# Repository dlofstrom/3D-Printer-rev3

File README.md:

# 3D Printer rev3

This repository contains all the source files for my 3D printer

More details about the build can be found at dlofstrom.wordpress.com

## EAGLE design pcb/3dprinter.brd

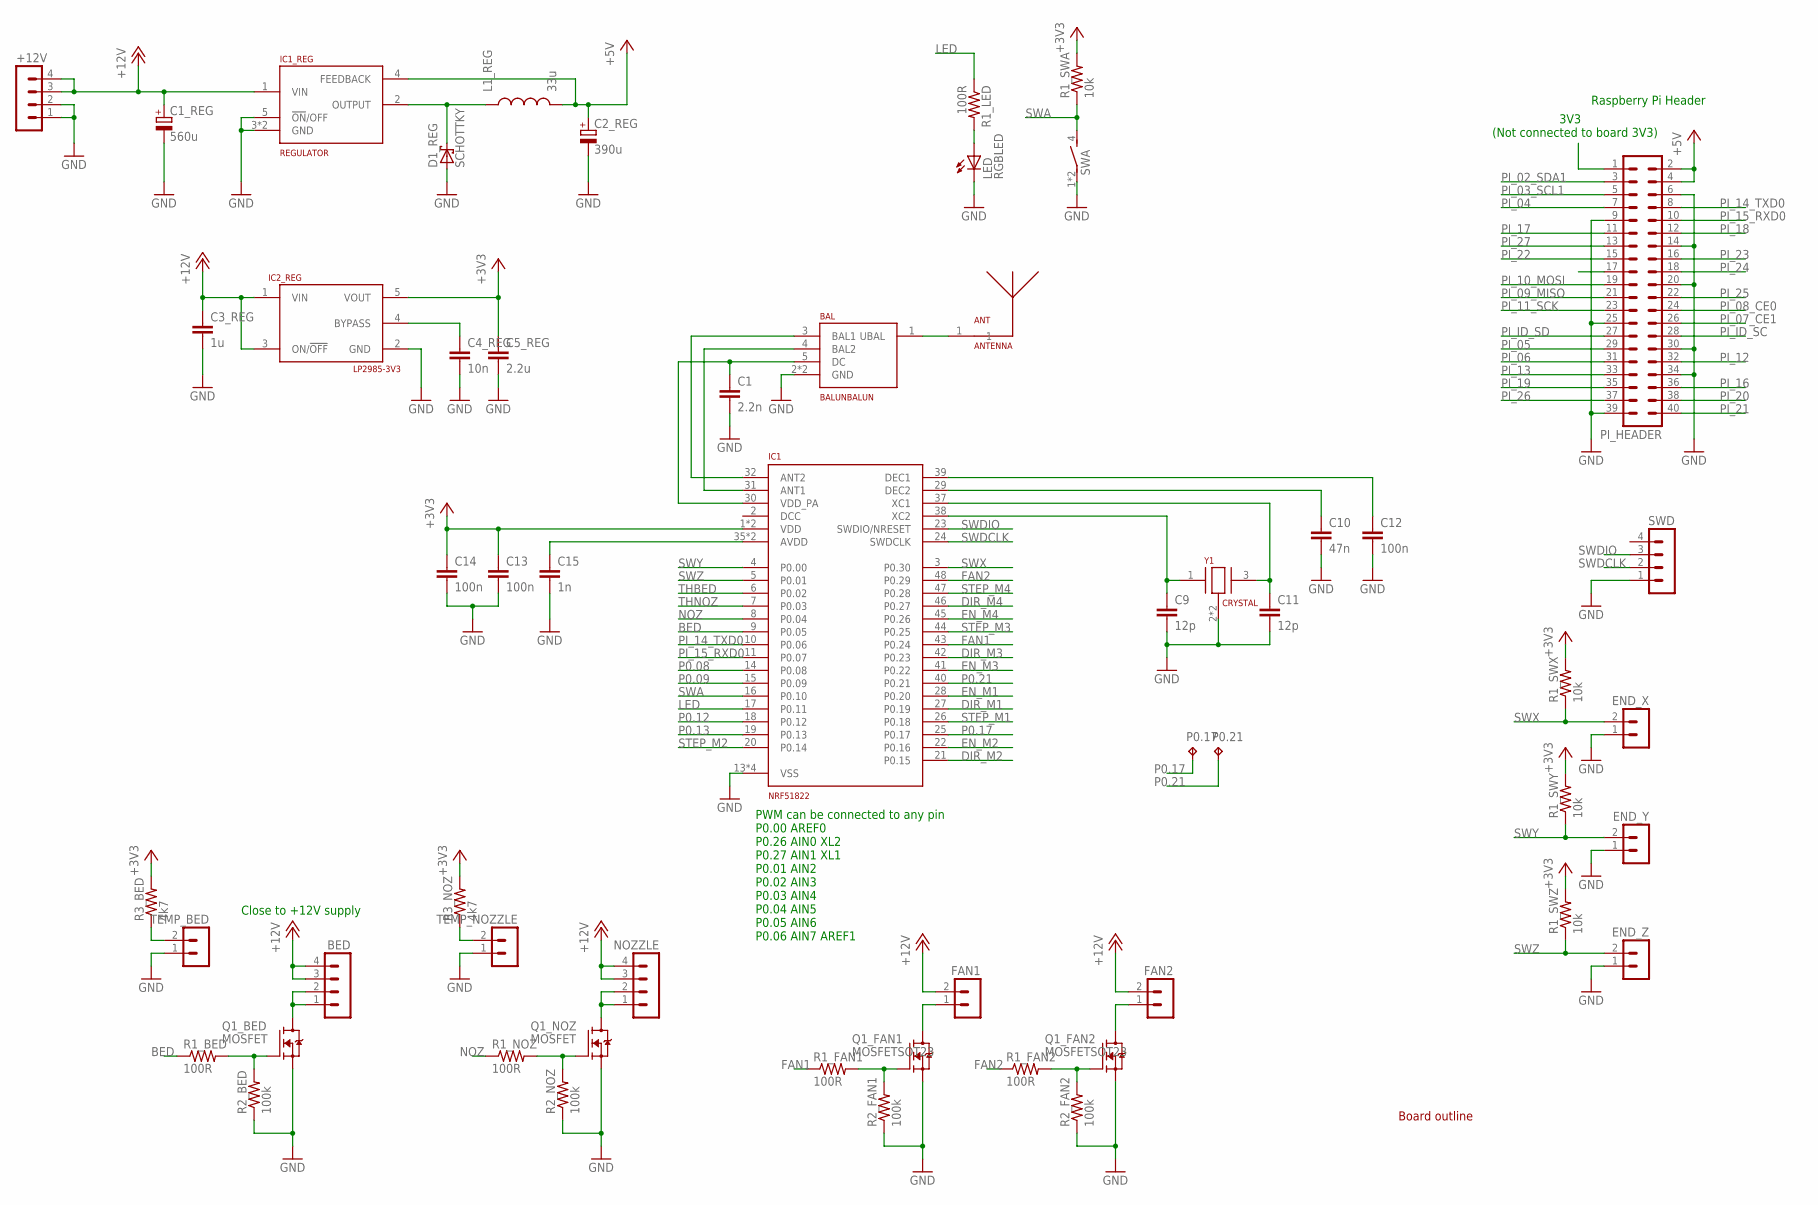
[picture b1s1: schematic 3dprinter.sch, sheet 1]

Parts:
+12V: MA04-15.08; MA04-1_5MM
ANT: ANTENNA
BAL: BALUNBALUN; BALUN
BED: MA04-12.54; MA04-1
C1: 2.2n; C0603
C1_REG: 560u; TANTULUM
C2_REG: 390u; TANTULUM
C3_REG: 1u; C0805
C4_REG: 10n; C0603
C5_REG: 2.2u; C0805
C9, C11: 12p; C0603
C10: 47n; C0603
C12, C13, C14: 100n; C0603
C15: 1n; C0603
D1_REG: SCHOTTKY
END_X: MA02-12.54; MA02-1
END_Y: MA02-12.54; MA02-1
END_Z: MA02-12.54; MA02-1
FAN1, FAN2: MA02-12.54; MA02-1
IC1: NRF51822; QFN48
IC1_REG: REGULATOR
IC2_REG: LP2985-3V3; SOT23
L1_REG: 33u; INDUCTOR
LED: RGBLED
NOZZLE: MA04-12.54; MA04-1
OUTLINE: OUTLINE
P0.17, P0.21: TPB1,27; B1,27
PI_HEADER: MA20-2
Q1_BED, Q1_NOZ: MOSFET
Q1_FAN1, Q1_FAN2: MOSFETSOT23; SOT23_FAN
R1_BED, R1_FAN1, R1_FAN2, R1_LED, R1_NOZ: 100R; R0603
R1_SWA, R1_SWX, R1_SWY, R1_SWZ: 10k; R0603
R2_BED, R2_FAN1, R2_FAN2, R2_NOZ: 100k; R0603
R3_BED, R3_NOZ: 4k7; R0603
SWA: BUTTON
SWD: MA04-12.54; MA04-1
TEMP_BED: MA02-12.54; MA02-1
TEMP_NOZZLE: MA02-12.54; MA02-1
Y1: CRYSTAL

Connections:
+3V3: C5_REG.1, C13.1, C14.1, IC1.1 (VDD), IC1.12 (VDD), IC2_REG.5 (VOUT), R1_SWA.2, R1_SWX.2, R1_SWY.2, R1_SWZ.2, R3_BED.2, R3_NOZ.2; also elsewhere on the board
+5V: C2_REG.+, IC1_REG.4 (FEEDBACK), L1_REG.2, PI_HEADER.2, PI_HEADER.4
+12V: +12V.3, +12V.4, BED.3, BED.4, C1_REG.+, C3_REG.1, FAN1.2, FAN2.2, IC1_REG.1 (VIN), IC2_REG.1 (VIN), IC2_REG.3 (ON/!OFF), NOZZLE.3, NOZZLE.4; also elsewhere on the board
ANT: ANT.1, BAL.1 (UBAL)
BED: IC1.9 (P0.05), R1_BED.1
BED-: BED.1, BED.2, Q1_BED.TAB (D)
BEDG: Q1_BED.4 (G), R1_BED.2, R2_BED.2
DIR_M1: IC1.27 (P0.19); also elsewhere on the board
DIR_M2: IC1.21 (P0.15); also elsewhere on the board
DIR_M3: IC1.42 (P0.23); also elsewhere on the board
DIR_M4: IC1.46 (P0.27); also elsewhere on the board
EN_M1: IC1.28 (P0.20); also elsewhere on the board
EN_M2: IC1.22 (P0.16); also elsewhere on the board
EN_M3: IC1.41 (P0.22); also elsewhere on the board
EN_M4: IC1.45 (P0.26); also elsewhere on the board
FAN1: IC1.43 (P0.24), R1_FAN1.1
FAN1-: FAN1.1, Q1_FAN1.3 (D)
FAN1G: Q1_FAN1.1 (G), R1_FAN1.2, R2_FAN1.2
FAN2: IC1.48 (P0.29), R1_FAN2.1
FAN2-: FAN2.1, Q1_FAN2.3 (D)
FAN2G: Q1_FAN2.1 (G), R1_FAN2.2, R2_FAN2.2
GND: +12V.1, +12V.2, BAL.2 (GND), BAL.6 (GND), C1.2, C1_REG.-, C2_REG.-, C3_REG.2, C4_REG.2, C5_REG.2, C9.2, C10.2, C11.2, C12.2, C13.2, C14.2, C15.2, D1_REG.A, END_X.1, END_Y.1, END_Z.1, IC1.13 (VSS), IC1.33 (VSS), IC1.34 (VSS), IC1.PAD (VSS), IC1_REG.3 (GND), IC1_REG.5 (!ON!/OFF), IC1_REG.TAB (GND), IC2_REG.2 (GND), LED.C, PI_HEADER.6, PI_HEADER.9, PI_HEADER.14, PI_HEADER.20, PI_HEADER.25, PI_HEADER.30, PI_HEADER.34, PI_HEADER.39, Q1_BED.1 (S), Q1_BED.2 (S), Q1_BED.3 (S), Q1_FAN1.2 (S), Q1_FAN2.2 (S), Q1_NOZ.1 (S), Q1_NOZ.2 (S), Q1_NOZ.3 (S), R2_BED.1, R2_FAN1.1, R2_FAN2.1, R2_NOZ.1, SWA.1, SWA.2 (1), SWD.1, TEMP_BED.1, TEMP_NOZZLE.1, Y1.2, Y1.4 (2); also elsewhere on the board
IC1_ANT1: BAL.3 (BAL1), IC1.32 (ANT2)
IC1_ANT2: BAL.4 (BAL2), IC1.31 (ANT1)
IC1_AVDD: C15.1, IC1.35 (AVDD), IC1.36 (AVDD)
IC1_DEC1: C12.1, IC1.39 (DEC1)
IC1_DEC2: C10.1, IC1.29 (DEC2)
IC1_REG_OUT: D1_REG.C, IC1_REG.2 (OUTPUT), L1_REG.1
IC1_VDD_PA: BAL.5 (DC), C1.1, IC1.30 (VDD_PA)
IC1_XC1: C11.1, IC1.37 (XC1), Y1.3
IC1_XC2: C9.1, IC1.38 (XC2), Y1.1
IC2_REG_BYPASS: C4_REG.1, IC2_REG.4 (BYPASS)
LED: IC1.17 (P0.11), R1_LED.1
LEDA: LED.A, R1_LED.2
NOZ: IC1.8 (P0.04), R1_NOZ.1
NOZ-: NOZZLE.1, NOZZLE.2, Q1_NOZ.TAB (D)
NOZG: Q1_NOZ.4 (G), R1_NOZ.2, R2_NOZ.2
P0.08: IC1.14 (P0.08)
P0.09: IC1.15 (P0.09)
P0.12: IC1.18 (P0.12)
P0.13: IC1.19 (P0.13)
P0.17: IC1.25 (P0.17), P0.17.TP
P0.21: IC1.40 (P0.21), P0.21.TP
PI_02_SDA1: PI_HEADER.3
PI_3V3: PI_HEADER.1
PI_3V32: PI_HEADER.17
PI_03_SCL1: PI_HEADER.5
PI_04: PI_HEADER.7
PI_05: PI_HEADER.29
PI_06: PI_HEADER.31
PI_07_CE1: PI_HEADER.26
PI_08_CE0: PI_HEADER.24
PI_09_MISO: PI_HEADER.21
PI_10_MOSI: PI_HEADER.19
PI_11_SCK: PI_HEADER.23
PI_12: PI_HEADER.32
PI_13: PI_HEADER.33
PI_14_TXD0: IC1.10 (P0.06), PI_HEADER.8
PI_15_RXD0: IC1.11 (P0.07), PI_HEADER.10
PI_16: PI_HEADER.36
PI_17: PI_HEADER.11
PI_18: PI_HEADER.12
PI_19: PI_HEADER.35
PI_20: PI_HEADER.38
PI_21: PI_HEADER.40
PI_22: PI_HEADER.15
PI_23: PI_HEADER.16
PI_24: PI_HEADER.18
PI_25: PI_HEADER.22
PI_26: PI_HEADER.37
PI_27: PI_HEADER.13
PI_ID_SC: PI_HEADER.28
PI_ID_SD: PI_HEADER.27
STEP_M1: IC1.26 (P0.18); also elsewhere on the board
STEP_M2: IC1.20 (P0.14); also elsewhere on the board
STEP_M3: IC1.44 (P0.25); also elsewhere on the board
STEP_M4: IC1.47 (P0.28); also elsewhere on the board
SWA: IC1.16 (P0.10), R1_SWA.1, SWA.4 (2)
SWDCLK: IC1.24 (SWDCLK), SWD.2
SWDIO: IC1.23 (SWDIO/NRESET), SWD.3
SWX: END_X.2, IC1.3 (P0.30), R1_SWX.1
SWY: END_Y.2, IC1.4 (P0.00), R1_SWY.1
SWZ: END_Z.2, IC1.5 (P0.01), R1_SWZ.1
THBED: IC1.6 (P0.02), R3_BED.1, TEMP_BED.2
THNOZ: IC1.7 (P0.03), R3_NOZ.1, TEMP_NOZZLE.2

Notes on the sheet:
Raspberry Pi Header
3V3 (Not connected to board 3V3)
Close to +12V supply
PWM can be connected to any pin P0.00 AREF0 P0.26 AIN0 XL2 P0.27 AIN1 XL1 P0.01 AIN2 P0.02 AIN3 P0.03 AIN4 P0.04 AIN5 P0.05 AIN6 P0.06 AIN7 AREF1

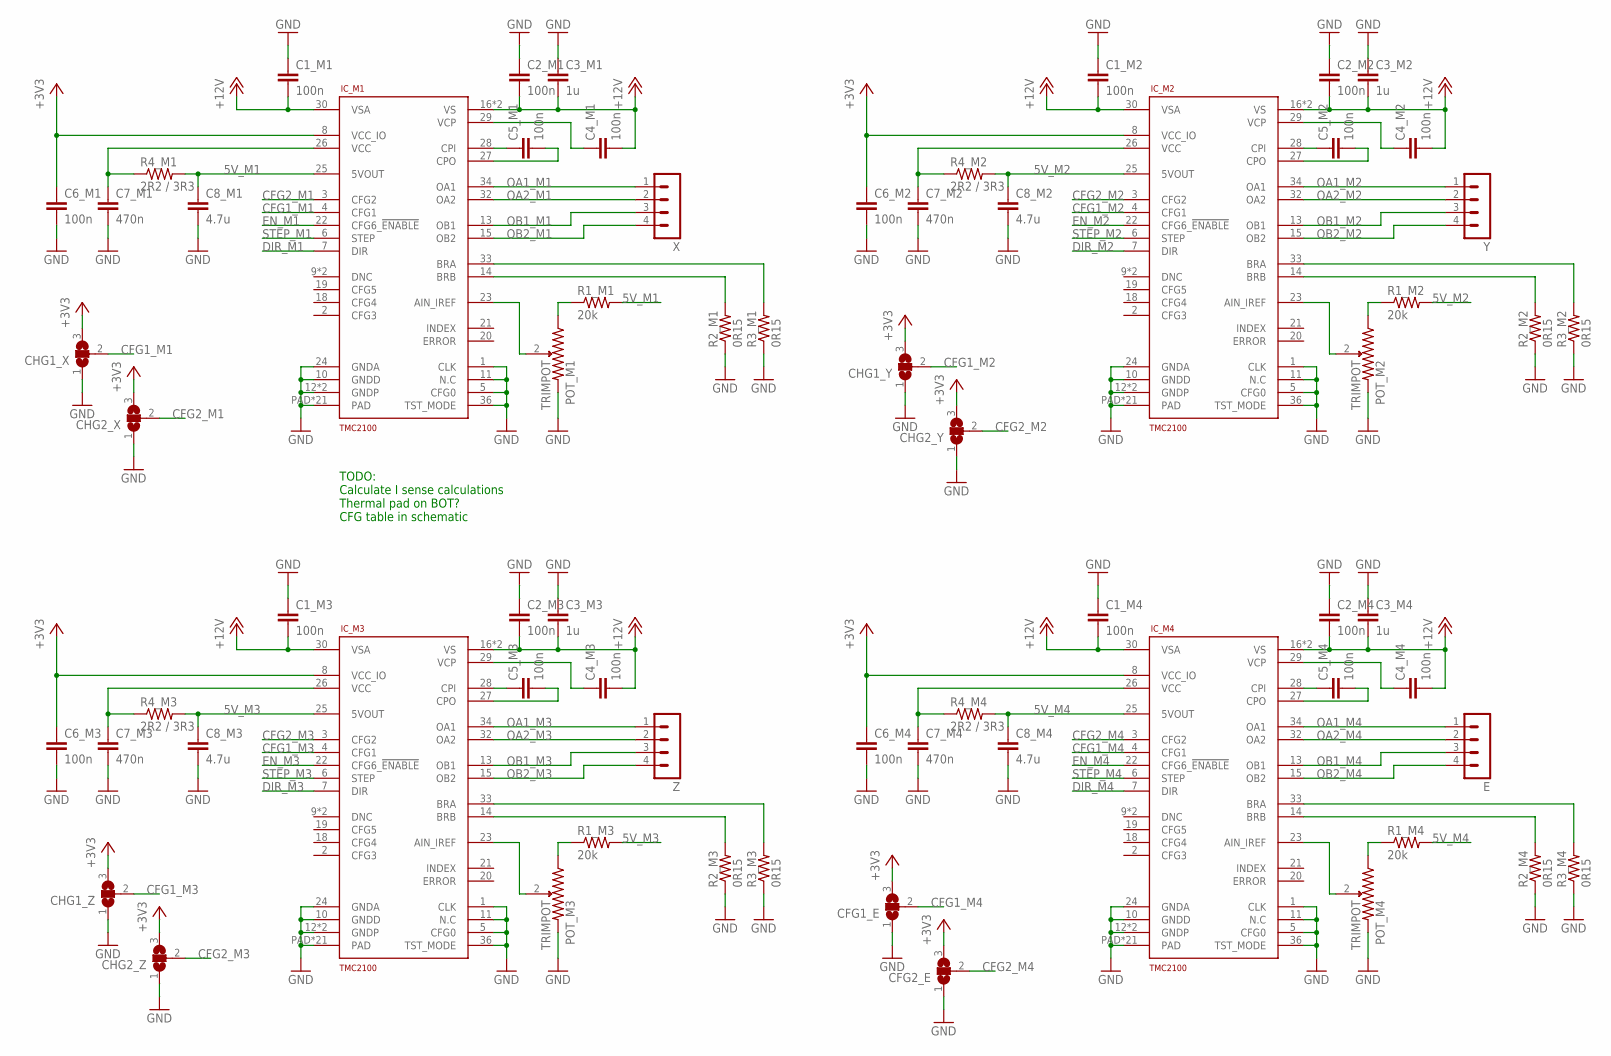
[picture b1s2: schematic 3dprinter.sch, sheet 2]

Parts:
C1_M1, C1_M2, C1_M3, C1_M4, C2_M1, C2_M2, C2_M3, C2_M4, C4_M1, C4_M2, C4_M3, C4_M4, C5_M1, C5_M2, C5_M3, C5_M4, C6_M1, C6_M2, C6_M3, C6_M4: 100n; C0603
C3_M1, C3_M2, C3_M3, C3_M4: 1u; C0603
C7_M1, C7_M2, C7_M3, C7_M4: 470n; C0603
C8_M1, C8_M2, C8_M3, C8_M4: 4.7u; C0603
CFG1_E, CFG2_E: SJ2W; SJ_2
CHG1_X, CHG1_Y, CHG1_Z, CHG2_X, CHG2_Y, CHG2_Z: SJ2W; SJ_2
E: MA04-12.54; MA04-1
IC_M1, IC_M2, IC_M3, IC_M4: TMC2100; QFN36
POT_M1, POT_M2, POT_M3, POT_M4: TRIMPOT
R1_M1, R1_M2, R1_M3, R1_M4: 20k; R0603
R2_M1, R2_M2, R2_M3, R2_M4, R3_M1, R3_M2, R3_M3, R3_M4: 0R15; R0805
R4_M1, R4_M2, R4_M3, R4_M4: 2R2 / 3R3; R0603
X: MA04-12.54; MA04-1
Y: MA04-12.54; MA04-1
Z: MA04-12.54; MA04-1

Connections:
5V_M1: C8_M1.1, IC_M1.25 (5VOUT), R1_M1.2, R4_M1.2
5V_M2: C8_M2.1, IC_M2.25 (5VOUT), R1_M2.2, R4_M2.2
5V_M3: C8_M3.1, IC_M3.25 (5VOUT), R1_M3.2, R4_M3.2
5V_M4: C8_M4.1, IC_M4.25 (5VOUT), R1_M4.2, R4_M4.2
+3V3: C6_M1.1, C6_M2.1, C6_M3.1, C6_M4.1, CFG1_E.3, CFG2_E.3, CHG1_X.3, CHG1_Y.3, CHG1_Z.3, CHG2_X.3, CHG2_Y.3, CHG2_Z.3, IC_M1.8 (VCC_IO), IC_M2.8 (VCC_IO), IC_M3.8 (VCC_IO), IC_M4.8 (VCC_IO); also elsewhere on the board
+12V: C1_M1.2, C1_M2.2, C1_M3.2, C1_M4.2, C2_M1.2, C2_M2.2, C2_M3.2, C2_M4.2, C3_M1.2, C3_M2.2, C3_M3.2, C3_M4.2, C4_M1.2, C4_M2.2, C4_M3.2, C4_M4.2, IC_M1.16 (VS), IC_M1.30 (VSA), IC_M1.31 (VS), IC_M2.16 (VS), IC_M2.30 (VSA), IC_M2.31 (VS), IC_M3.16 (VS), IC_M3.30 (VSA), IC_M3.31 (VS), IC_M4.16 (VS), IC_M4.30 (VSA), IC_M4.31 (VS); also elsewhere on the board
AIN_M1: IC_M1.23 (AIN_IREF), POT_M1.2
AIN_M2: IC_M2.23 (AIN_IREF), POT_M2.2
AIN_M3: IC_M3.23 (AIN_IREF), POT_M3.2
AIN_M4: IC_M4.23 (AIN_IREF), POT_M4.2
BRA_M1: IC_M1.33 (BRA), R3_M1.2
BRA_M2: IC_M2.33 (BRA), R3_M2.2
BRA_M3: IC_M3.33 (BRA), R3_M3.2
BRA_M4: IC_M4.33 (BRA), R3_M4.2
BRB_M1: IC_M1.14 (BRB), R2_M1.2
BRB_M2: IC_M2.14 (BRB), R2_M2.2
BRB_M3: IC_M3.14 (BRB), R2_M3.2
BRB_M4: IC_M4.14 (BRB), R2_M4.2
CFG1_M1: CHG1_X.2, IC_M1.4 (CFG1)
CFG1_M2: CHG1_Y.2, IC_M2.4 (CFG1)
CFG1_M3: CHG1_Z.2, IC_M3.4 (CFG1)
CFG1_M4: CFG1_E.2, IC_M4.4 (CFG1)
CFG2_M1: CHG2_X.2, IC_M1.3 (CFG2)
CFG2_M2: CHG2_Y.2, IC_M2.3 (CFG2)
CFG2_M3: CHG2_Z.2, IC_M3.3 (CFG2)
CFG2_M4: CFG2_E.2, IC_M4.3 (CFG2)
CPI_M1: C5_M1.1, IC_M1.28 (CPI)
CPI_M2: C5_M2.1, IC_M2.28 (CPI)
CPI_M3: C5_M3.1, IC_M3.28 (CPI)
CPI_M4: C5_M4.1, IC_M4.28 (CPI)
CPO_M1: C5_M1.2, IC_M1.27 (CPO)
CPO_M2: C5_M2.2, IC_M2.27 (CPO)
CPO_M3: C5_M3.2, IC_M3.27 (CPO)
CPO_M4: C5_M4.2, IC_M4.27 (CPO)
DIR_M1: IC_M1.7 (DIR); also elsewhere on the board
DIR_M2: IC_M2.7 (DIR); also elsewhere on the board
DIR_M3: IC_M3.7 (DIR); also elsewhere on the board
DIR_M4: IC_M4.7 (DIR); also elsewhere on the board
EN_M1: IC_M1.22 (CFG6_!ENABLE); also elsewhere on the board
EN_M2: IC_M2.22 (CFG6_!ENABLE); also elsewhere on the board
EN_M3: IC_M3.22 (CFG6_!ENABLE); also elsewhere on the board
EN_M4: IC_M4.22 (CFG6_!ENABLE); also elsewhere on the board
GND: C1_M1.1, C1_M2.1, C1_M3.1, C1_M4.1, C2_M1.1, C2_M2.1, C2_M3.1, C2_M4.1, C3_M1.1, C3_M2.1, C3_M3.1, C3_M4.1, C6_M1.2, C6_M2.2, C6_M3.2, C6_M4.2, C7_M1.2, C7_M2.2, C7_M3.2, C7_M4.2, C8_M1.2, C8_M2.2, C8_M3.2, C8_M4.2, CFG1_E.1, CFG2_E.1, CHG1_X.1, CHG1_Y.1, CHG1_Z.1, CHG2_X.1, CHG2_Y.1, CHG2_Z.1, IC_M1.1 (CLK), IC_M1.5 (CFG0), IC_M1.10 (GNDD), IC_M1.11 (N.C), IC_M1.12 (GNDP), IC_M1.24 (GNDA), IC_M1.35 (GNDP), IC_M1.36 (TST_MODE), IC_M1.PAD, IC_M1.TVIA1 (PAD), IC_M1.TVIA2 (PAD), IC_M1.TVIA3 (PAD), IC_M1.TVIA4 (PAD), IC_M1.TVIA5 (PAD), IC_M1.TVIA6 (PAD), IC_M1.TVIA7 (PAD), IC_M1.TVIA8 (PAD), IC_M1.TVIA9 (PAD), IC_M1.TVIA10 (PAD), IC_M1.TVIA11 (PAD), IC_M1.TVIA12 (PAD), IC_M1.TVIA13 (PAD), IC_M1.TVIA14 (PAD), IC_M1.TVIA15 (PAD), IC_M1.TVIA16 (PAD), IC_M1.TVIA17 (PAD), IC_M1.TVIA18 (PAD), IC_M1.TVIA19 (PAD), IC_M1.TVIA20 (PAD), IC_M2.1 (CLK), IC_M2.5 (CFG0), IC_M2.10 (GNDD), IC_M2.11 (N.C), IC_M2.12 (GNDP), IC_M2.24 (GNDA), IC_M2.35 (GNDP), IC_M2.36 (TST_MODE), IC_M2.PAD, IC_M2.TVIA1 (PAD), IC_M2.TVIA2 (PAD), IC_M2.TVIA3 (PAD), IC_M2.TVIA4 (PAD), IC_M2.TVIA5 (PAD), IC_M2.TVIA6 (PAD), IC_M2.TVIA7 (PAD), IC_M2.TVIA8 (PAD), IC_M2.TVIA9 (PAD), IC_M2.TVIA10 (PAD), IC_M2.TVIA11 (PAD), IC_M2.TVIA12 (PAD), IC_M2.TVIA13 (PAD), IC_M2.TVIA14 (PAD), IC_M2.TVIA15 (PAD), IC_M2.TVIA16 (PAD), IC_M2.TVIA17 (PAD), IC_M2.TVIA18 (PAD), IC_M2.TVIA19 (PAD), IC_M2.TVIA20 (PAD), IC_M3.1 (CLK), IC_M3.5 (CFG0), IC_M3.10 (GNDD), IC_M3.11 (N.C), IC_M3.12 (GNDP), IC_M3.24 (GNDA), IC_M3.35 (GNDP), IC_M3.36 (TST_MODE), IC_M3.PAD, IC_M3.TVIA1 (PAD), IC_M3.TVIA2 (PAD), IC_M3.TVIA3 (PAD), IC_M3.TVIA4 (PAD), IC_M3.TVIA5 (PAD), IC_M3.TVIA6 (PAD), IC_M3.TVIA7 (PAD), IC_M3.TVIA8 (PAD), IC_M3.TVIA9 (PAD), IC_M3.TVIA10 (PAD), IC_M3.TVIA11 (PAD), IC_M3.TVIA12 (PAD), IC_M3.TVIA13 (PAD), IC_M3.TVIA14 (PAD), IC_M3.TVIA15 (PAD), IC_M3.TVIA16 (PAD), IC_M3.TVIA17 (PAD), IC_M3.TVIA18 (PAD), IC_M3.TVIA19 (PAD), IC_M3.TVIA20 (PAD), IC_M4.1 (CLK), IC_M4.5 (CFG0), IC_M4.10 (GNDD), IC_M4.11 (N.C), IC_M4.12 (GNDP), IC_M4.24 (GNDA), IC_M4.35 (GNDP), IC_M4.36 (TST_MODE), IC_M4.PAD, IC_M4.TVIA1 (PAD), IC_M4.TVIA2 (PAD), IC_M4.TVIA3 (PAD), IC_M4.TVIA4 (PAD), IC_M4.TVIA5 (PAD), IC_M4.TVIA6 (PAD), IC_M4.TVIA7 (PAD), IC_M4.TVIA8 (PAD), IC_M4.TVIA9 (PAD), IC_M4.TVIA10 (PAD), IC_M4.TVIA11 (PAD), IC_M4.TVIA12 (PAD), IC_M4.TVIA13 (PAD), IC_M4.TVIA14 (PAD), IC_M4.TVIA15 (PAD), IC_M4.TVIA16 (PAD), IC_M4.TVIA17 (PAD), IC_M4.TVIA18 (PAD), IC_M4.TVIA19 (PAD), IC_M4.TVIA20 (PAD), POT_M1.3, POT_M2.3, POT_M3.3, POT_M4.3, R2_M1.1, R2_M2.1, R2_M3.1, R2_M4.1, R3_M1.1, R3_M2.1, R3_M3.1, R3_M4.1; also elsewhere on the board
OA1_M1: IC_M1.34 (OA1), X.1
OA1_M2: IC_M2.34 (OA1), Y.1
OA1_M3: IC_M3.34 (OA1), Z.1
OA1_M4: E.1, IC_M4.34 (OA1)
OA2_M1: IC_M1.32 (OA2), X.2
OA2_M2: IC_M2.32 (OA2), Y.2
OA2_M3: IC_M3.32 (OA2), Z.2
OA2_M4: E.2, IC_M4.32 (OA2)
OB1_M1: IC_M1.13 (OB1), X.3
OB1_M2: IC_M2.13 (OB1), Y.3
OB1_M3: IC_M3.13 (OB1), Z.3
OB1_M4: E.3, IC_M4.13 (OB1)
OB2_M1: IC_M1.15 (OB2), X.4
OB2_M2: IC_M2.15 (OB2), Y.4
OB2_M3: IC_M3.15 (OB2), Z.4
OB2_M4: E.4, IC_M4.15 (OB2)
POT_M1: POT_M1.1, R1_M1.1
POT_M2: POT_M2.1, R1_M2.1
POT_M3: POT_M3.1, R1_M3.1
POT_M4: POT_M4.1, R1_M4.1
STEP_M1: IC_M1.6 (STEP); also elsewhere on the board
STEP_M2: IC_M2.6 (STEP); also elsewhere on the board
STEP_M3: IC_M3.6 (STEP); also elsewhere on the board
STEP_M4: IC_M4.6 (STEP); also elsewhere on the board
VCC_M1: C7_M1.1, IC_M1.26 (VCC), R4_M1.1
VCC_M2: C7_M2.1, IC_M2.26 (VCC), R4_M2.1
VCC_M3: C7_M3.1, IC_M3.26 (VCC), R4_M3.1
VCC_M4: C7_M4.1, IC_M4.26 (VCC), R4_M4.1
VCP_M1: C4_M1.1, IC_M1.29 (VCP)
VCP_M2: C4_M2.1, IC_M2.29 (VCP)
VCP_M3: C4_M3.1, IC_M3.29 (VCP)
VCP_M4: C4_M4.1, IC_M4.29 (VCP)

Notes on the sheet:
TODO: Calculate I sense calculations Thermal pad on BOT? CFG table in schematic

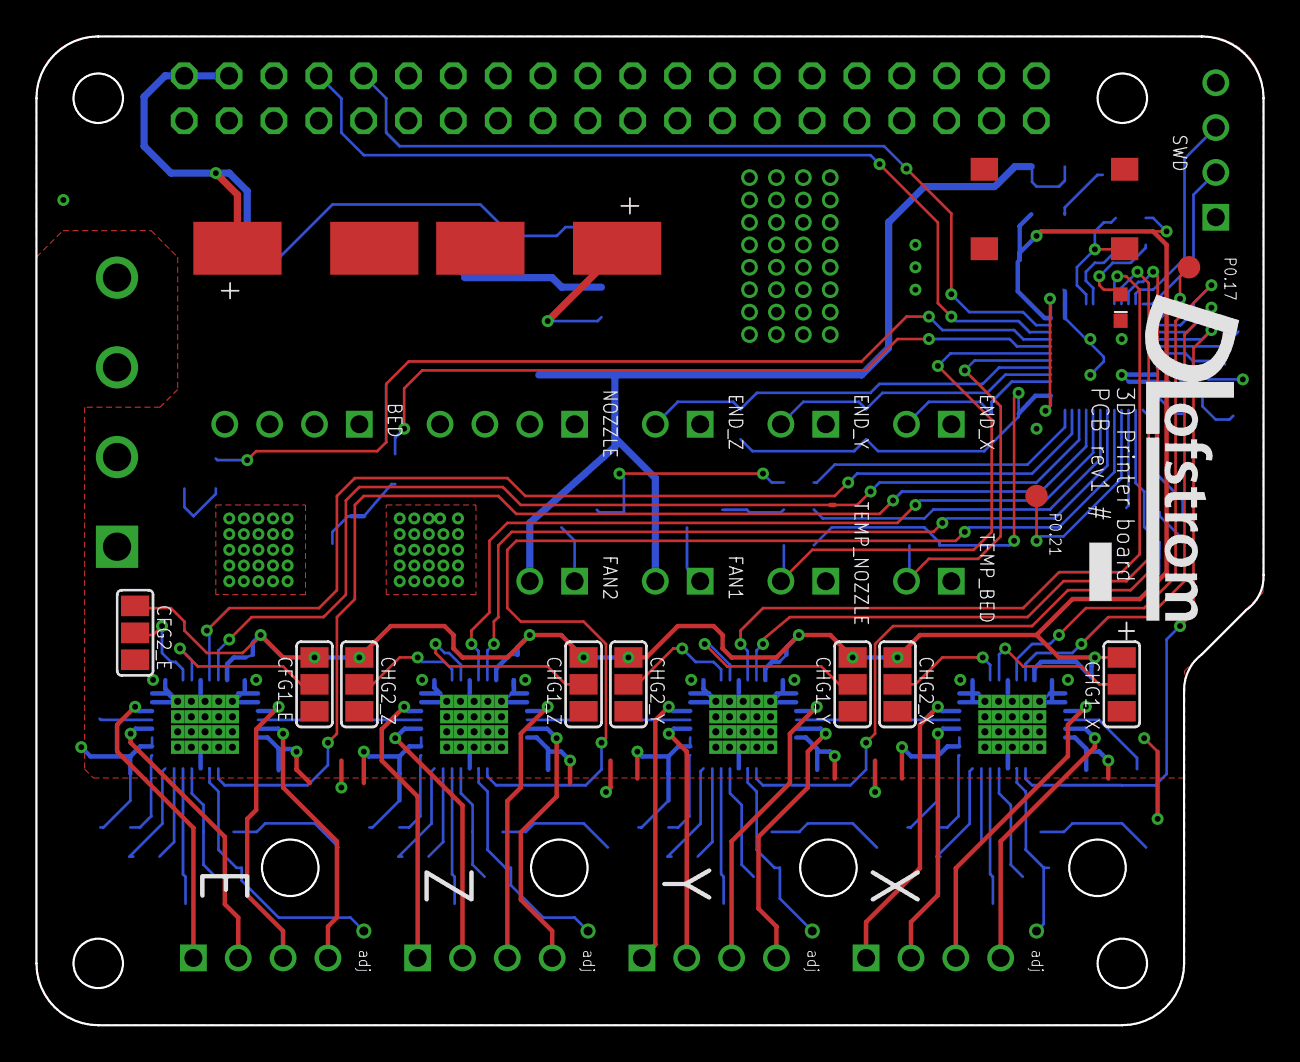
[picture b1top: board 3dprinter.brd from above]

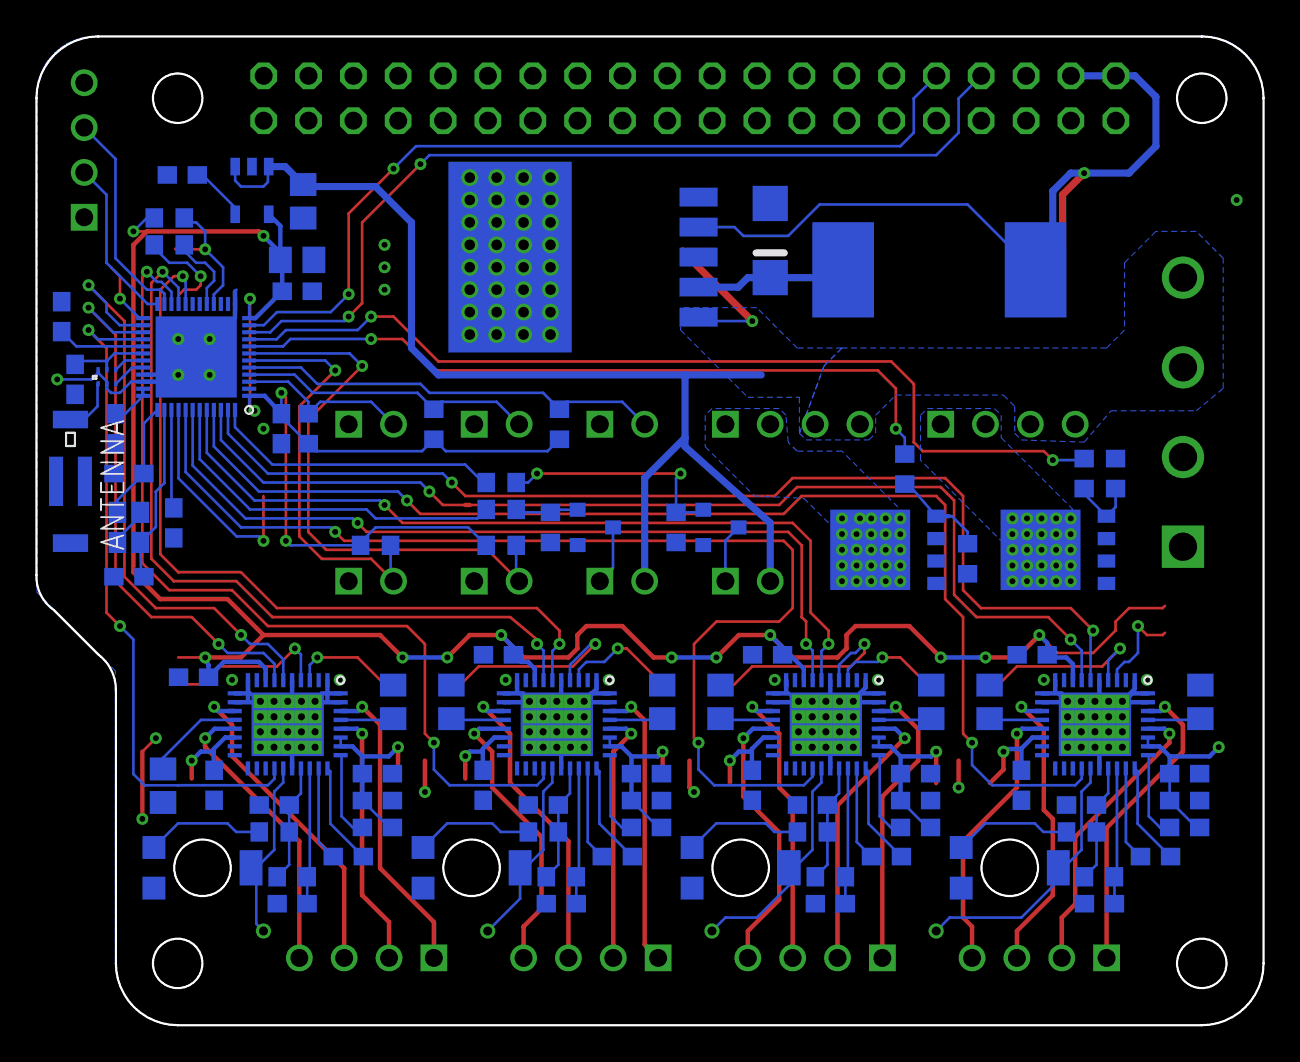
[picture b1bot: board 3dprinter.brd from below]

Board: 2 copper layers, 69.5 x 56.0 mm, 125 parts (94 on the bottom side), 113 nets.

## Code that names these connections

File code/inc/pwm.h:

//
// pwm.h
//


#ifndef PWM_H
#define PWM_H

#include <stdbool.h>
#include <stdint.h>
#include <stdio.h>
#include <string.h>

#define NOZ_PIN 4
#define NOZ_PWM_CHANNEL 0
#define BED_PIN 5
#define BED_PWM_CHANNEL 1
#define FAN1_PIN 24
#define FAN1_PWM_CHANNEL 2
#define FAN2_PIN 29

//Initialize pwm
void pwm_init(void);
void pwm_set_duty(uint32_t channel, uint32_t value);

#endif

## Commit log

2016-08-19 Added .dxf files for laser cutting
2016-08-19 3D printed cornerpiece added
2016-10-03 XY shft assembly, stl files
2016-10-18 XY assembly revisited and updated stl files
2016-11-30 stls for Z axis, bed frame and adjusments for belts
2017-02-17 Updated stl files
2017-02-22 Moves and added holes for end stops
2017-02-23 Arduino code for evaluating stepper drivers, initial commit
2017-02-23 Playing around with pyaudio for analyzing stepper sound
2017-02-24 DRV8825 test microstep
2017-02-25 Added A4983 test code
2017-03-02 Added TMC2100 test case
2017-03-06 Modified gitignore for Eagle files
2017-03-06 Initial PCB dimensions
2017-03-07 Footprint of TMC2100 and reference schematic added
2017-03-07 TMC2100 initial routing
2017-03-11 Added NRF51822 footprint
2017-03-12 Example circuit nrf51 passives
2017-03-29 Updated gitignore
2017-03-29 Added stl files
2017-03-30 Added Bed as printable pdf
2017-04-08 Multiplied motor driver circuit and added mosfets
2017-04-12 Updated mosfet
2017-04-19 Added regulator and fan mosfet
2017-04-19 Started component placment
2017-04-20 Rough component placement and started routing
2017-04-21 More routing
2017-04-26 Component placement done, started final routing
2017-04-28 Final routing first pass
2017-04-29 Final routing, wire width, via drill, DRC approved
2017-04-29 Added button and led
2017-04-29 Setup nrf51 sdk and build tools
2017-05-03 Added testpads ERC/DRC OK
2017-05-03 Top/Bot silkscreen and clearance
2017-05-03 First gerber generation for review
2017-05-05 Silk screen
2017-05-05 Gerber generated
2017-05-05 Added BOM
2017-05-05 Cleaned library from unused packages
2017-05-05 Added assembly data to library
2017-05-05 Added assembly drawing
2017-05-05 Cleaned BOM for assembly
2017-05-08 Added instructions for Octoprint setup
2017-05-08 Readme fix
2017-05-09 Remove temporary file
2017-05-17 A script for generating G-code functionality
2017-05-17 Code for G-code functionality generated and a small test program for testing command parsing and handling
2017-05-17 Fix stdint problem on Windows
2017-05-21 First blink example moved out of sdk examples, working on nrf51822 breakout board
2017-06-01 Sorted by package and value
2017-06-01 Stencil vector
2017-06-01 Schematic PDF
2017-06-01 First blink example on assembled PCB
2017-06-01 Uart read line and write functionality added, small example in main
2017-06-06 Printable schematic pdf
2017-06-06 First simple adc implementation, only one channel and not using interrupt
2017-06-07 adc test using interrupt, still only one channel
2017-06-09 ADC channel initialization and multi channel sampling, still untested
2017-06-11 ADC channel initialization and multi channel sampling, tested
2017-06-15 Timer functionality added, a ms counter available (millis)
2017-06-26 Soft PWM using Timer 2 on nozzle, bed and fan1.
2017-07-03 Modified adc and timer code so that it does not use drv libraries
2017-07-03 Modified ADC code for continous sampling from timer
2017-07-03 Fixed ms counting (overflow bug) and sampling adc continuously
2017-07-03 PWM frequency changed
2017-07-03 Test application in main to suppory recent changes
2017-07-05 Added printf format support to uart print
2017-07-05 Endstop read
2017-07-05 Stepper functionality
2017-07-05 Test for switch and stepper
2017-07-07 Changed code stucture
2017-07-07 Moved MCU specific code to peripheral files
2017-07-07 Changes so that G-code parsing is compiling and working on both NRF51 and computer
2017-07-07 Debug print only in debug mode to separate debug prints from real uart communication
2017-07-07 Debug mode can be compiled via make debug
2017-07-08 Rename old blinky files
2017-07-11 First simple example for writing and reading from flash memory
2017-07-13 First test with RTT print instead of UART for debugging
2017-07-13 RTT printing now working for debug print
2017-07-13 Rewrote uart driver, app_uart caused some error when powering down pi
2017-07-13 Moved checksum calculation from old code into gcode_functions and made first sucessful communication with OctoPrint (M110 returned ok)
2017-08-04 Code structure for application
2017-08-04 Uart is printed over RTT when debugging
2017-08-04 Line number increment
2017-08-04 Started to fill in ok responses to some g-code commands
2017-08-04 Report thermistor temperature working
2017-08-06 Added support for floating gcode parameters
2017-08-06 Begin to fill settings struct
2017-08-06 Started solving the linear movement by handling G91/G90 and started on G1, step calculation seems to work, interpolation still needed
2017-08-08 Moved uart buffers into functions
2017-08-08 More work on linear movement
2017-08-08 Linear movement first draft
2017-08-10 Axis movement connected to steppers, not tested
2017-08-10 Changed axit initialization for readability and security if future fields are added
2017-08-24 Removed excessive debug print
2017-08-24 Started code for temperature regulation
2017-08-30 Moved ok prints into printer functions
2017-08-30 Added a save function feature to wait for movement to finish before running anything else
2017-09-01 Reset functionality
2017-09-04 PID regulator working, tuning and thermistor pull-up/LUT needs to be updated
2017-09-05 Updated lookup for 4.7k pull up
2017-09-05 Temperature regulation more stable
2017-09-05 Changed pull up resistor for thermistor
2017-09-05 More work on regulation, looking for temperature spike bug
2017-09-06 TAGS in gitignore
2017-09-06 update temperature continuously
2017-09-06 Heater wait functionality
2017-09-06 Regulator more reliable and wait working
2017-09-13 Reset all added to printer reset function
2017-09-13 Changed pwm frequency
2017-09-14 pwm period changed to reduce mosfet temperature
2017-09-14 tuning axis reset and directions
2017-09-14 Fix reset all again
2017-09-18 Feedrate now working, not super fast but still ok
2017-09-19 Lots of functionality added for test run with gcode file, gcode functions, timeout disable, tuning and more
2017-09-20 LICENSE
2017-09-22 Tuning
2017-10-04 Added code todo list
2017-10-04 Updated checklist
2017-10-04 G0 rapid moves as fast as possible
2017-10-04 Added task to checklist
2017-10-18 Clearing buffer item when done maybe fixes command loop bug, not tested
2017-10-18 Increasing timer frequency to be able to move faster, not tested
2018-01-17 Movement now a little faster but stable, faster timer frequency wont work
2019-05-09 New mount for power supply (Mean well HRP-200-12)
